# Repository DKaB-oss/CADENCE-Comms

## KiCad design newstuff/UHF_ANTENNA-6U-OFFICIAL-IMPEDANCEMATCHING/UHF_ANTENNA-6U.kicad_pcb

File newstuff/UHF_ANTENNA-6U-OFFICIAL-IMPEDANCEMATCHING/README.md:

CADENCE UHF/L1 BANDS ANTENNA BOARD

6-layer PCB designed for CADENCE's UHF canted turnstile antenna and GPS L1 patch antenna. The board contains the UHF phasing network, antenna impedance-matching circuitry, power circuitry, and a burn-wire deployment circuit.

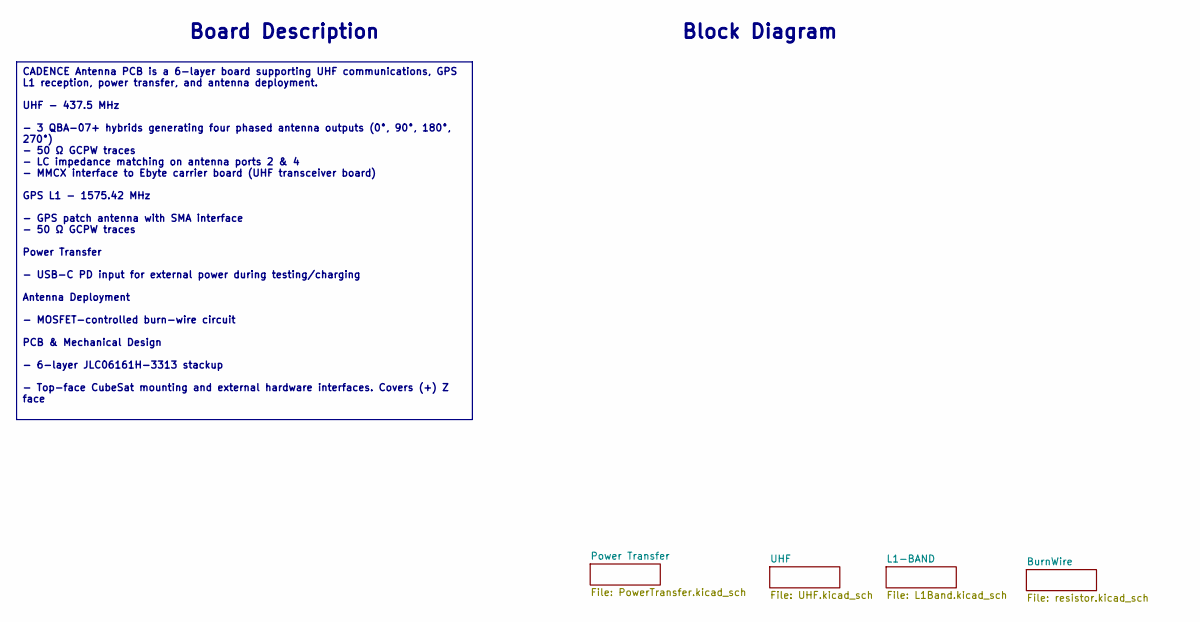
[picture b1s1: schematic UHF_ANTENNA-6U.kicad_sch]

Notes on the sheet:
Board Description
Block Diagram
CADENCE Antenna PCB is a 6-layer board supporting UHF communications, GPS L1 reception, power transfer, and antenna deployment. UHF - 437.5 MHz - 3 QBA-07+ hybrids generating four phased antenna outputs (0°, 90°, 180°, 270°) - 50 Ω GCPW traces - LC impedance matching on antenna ports 2 & 4 - MMCX i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

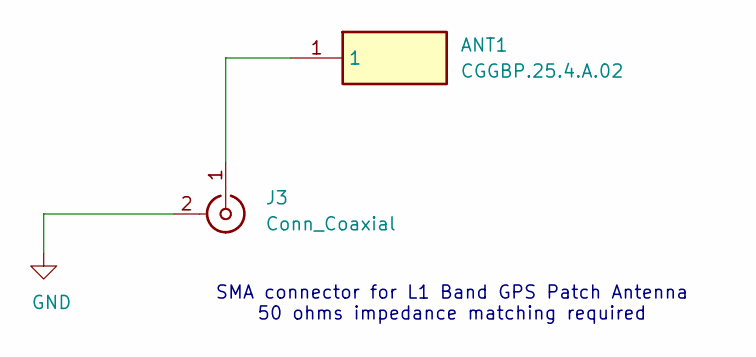
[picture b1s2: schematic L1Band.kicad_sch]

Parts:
ANT1: CGGBP.25.4.A.02; CGGBP254A02; Mouser Part Number 960-CGGBP.25.4.A.02
J3: Conn_Coaxial; SMA_Amphenol_132134-11_Vertical

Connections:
GND: J3.2 (Ext); also elsewhere on the board
unnamed: ANT1.1 (1_1), J3.1 (In)

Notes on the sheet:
SMA connector for L1 Band GPS Patch Antenna 50 ohms impedance matching required

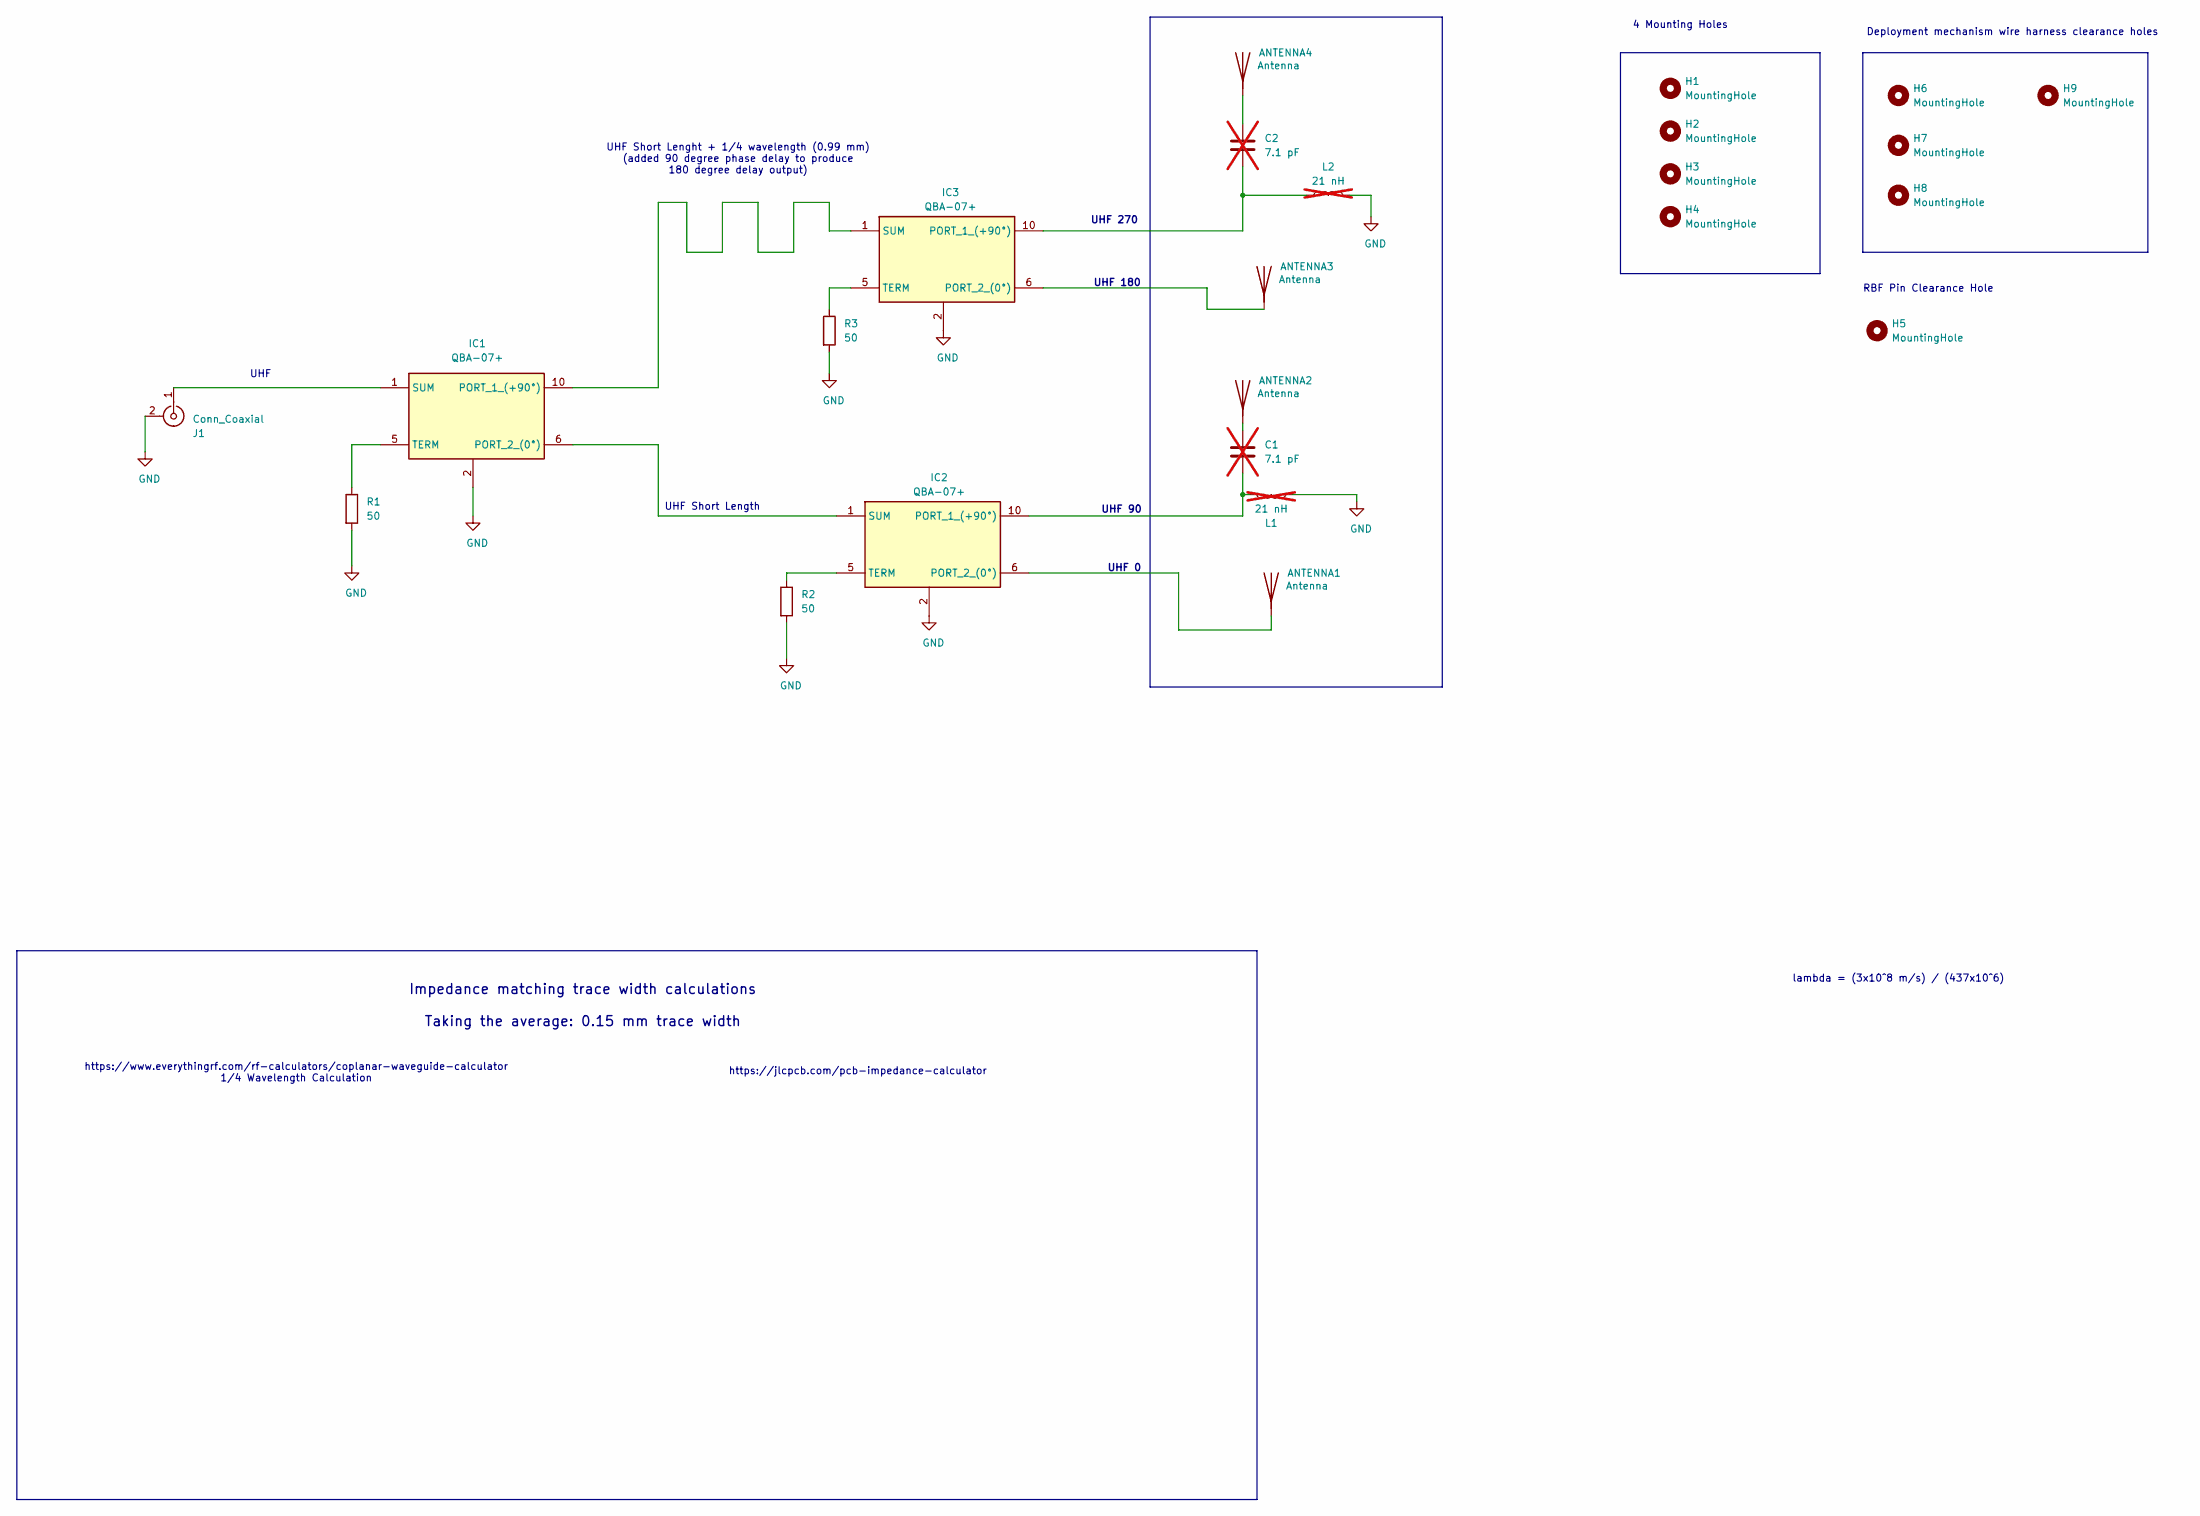
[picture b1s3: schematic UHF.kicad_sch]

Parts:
ANTENNA1, ANTENNA2, ANTENNA3, ANTENNA4: Antenna; SolderWirePad_1x01_SMD_5x10mm
C1, C2: 7.1 pF; C_0603_1608Metric; not fitted
H1, H2, H3, H4, H5: MountingHole; MountingHole_3.2mm_M3
H6, H7, H8, H9: MountingHole; MountingHole_2.7mm_M2.5_Pad
IC1, IC2, IC3: QBA-07+; QBA07; Manufacturer_Part_Number QBA-07+
J1: Conn_Coaxial; WR-MMCX_Wuerth_66012102111404_Vertical
L1, L2: 21 nH; L_0603_1608Metric; not fitted
R1, R2, R3: 50; R_0603_1608Metric

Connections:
GND: IC1.2, IC1.3 (GROUND_2), IC1.4 (GROUND_3), IC1.7 (GROUND_4), IC1.8 (GROUND_5), IC1.9 (GROUND_6), IC2.2, IC2.3 (GROUND_2), IC2.4 (GROUND_3), IC2.7 (GROUND_4), IC2.8 (GROUND_5), IC2.9 (GROUND_6), IC3.2, IC3.3 (GROUND_2), IC3.4 (GROUND_3), IC3.7 (GROUND_4), IC3.8 (GROUND_5), IC3.9 (GROUND_6), J1.2 (Ext), L1.1, L2.2, R1.2, R2.2, R3.2; also elsewhere on the board
unnamed: ANTENNA1.1 (A_1), IC2.6 (PORT_2_(0°))
unnamed: ANTENNA2.1 (A_1), C1.2
unnamed: ANTENNA3.1 (A_1), IC3.6 (PORT_2_(0°))
unnamed: ANTENNA4.1 (A_1), C2.1
unnamed: IC1.10 (PORT_1_(+90°)), IC3.1 (SUM)
unnamed: IC1.6 (PORT_2_(0°)), IC2.1 (SUM)
unnamed: IC1.1 (SUM), J1.1 (In)
unnamed: IC1.5 (TERM), R1.1
unnamed: C1.1, IC2.10 (PORT_1_(+90°)), L1.2
unnamed: IC2.5 (TERM), R2.1
unnamed: C2.2, IC3.10 (PORT_1_(+90°)), L2.1
unnamed: IC3.5 (TERM), R3.1

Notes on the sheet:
UHF
https://www.everythingrf.com/rf-calculators/coplanar-waveguide-calculator 1/4 Wavelength Calculation
UHF Short Length
UHF Short Lenght + 1/4 wavelength (0.99 mm) (added 90 degree phase delay to produce 180 degree delay output)
lambda = (3x10^8 m/s) / (437x10^6)
UHF 90
UHF 270
Impedance matching trace width calculations Taking the average: 0.15 mm trace width
RBF Pin Clearance Hole
UHF 0
UHF 180
https://jlcpcb.com/pcb-impedance-calculator
Deployment mechanism wire harness clearance holes
4 Mounting Holes

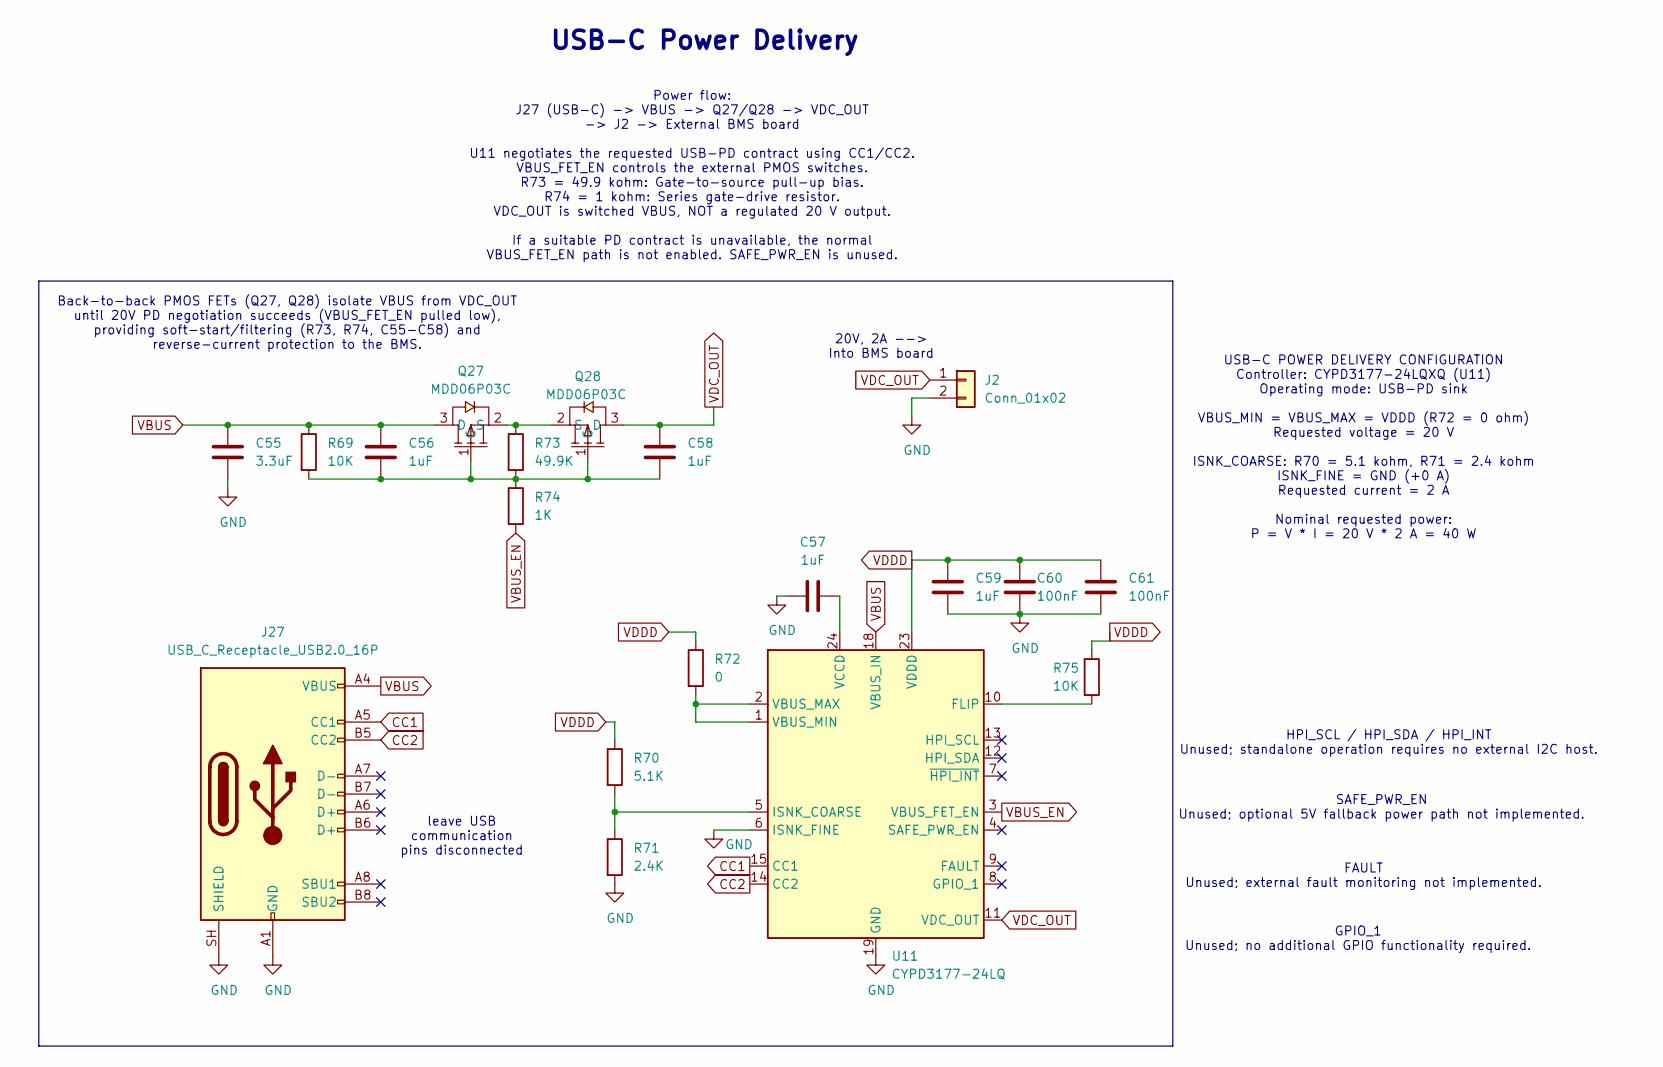
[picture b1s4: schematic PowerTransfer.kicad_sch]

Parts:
C55: 3.3uF; C_0805_2012Metric
C56, C57, C58, C59: 1uF; C_0805_2012Metric
C60, C61: 100nF; C_0603_1608Metric
J2: Conn_01x02; TerminalBlock_RND_205-00276_1x02_P5.00mm_Vertical
J27: USB_C_Receptacle_USB2.0_16P; USB_C_Receptacle_GCT_USB4110
Q27, Q28: MDD06P03C; SOT-23-3L_L2.9-W1.6-P1.90-LS2.8-BL; MPN MDD06P03C; LCSC Part C53069233
R69: 10K; R_0603_1608Metric_Pad0.98x0.95mm_HandSolder
R70: 5.1K; R_0603_1608Metric_Pad0.98x0.95mm_HandSolder
R71: 2.4K; R_0603_1608Metric
R72: 0; R_0603_1608Metric
R73: 49.9K; R_0603_1608Metric
R74: 1K; R_0603_1608Metric
R75: 10K; R_0603_1608Metric
U11: CYPD3177-24LQ; QFN-24-1EP_4x4mm_P0.5mm_EP2.75x2.75mm

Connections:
CC1: J27.A5 (CC1), U11.15 (CC1)
CC2: J27.B5 (CC2), U11.14 (CC2)
GND: C55.2, C57.2, C59.2, C60.2, C61.2, J2.2, J27.A1 (GND), J27.A12 (GND), J27.B1 (GND), J27.B12 (GND), J27.SH (SHIELD), R71.2, U11.6 (ISNK_FINE), U11.19 (GND), U11.22 (GND), U11.25 (GND); also elsewhere on the board
unnamed: C56.2, C58.2, Q27.1 (G), Q28.1 (G), R69.2, R73.2, R74.1
unnamed: Q27.2 (S), Q28.2 (S), R73.1
unnamed: R75.2, U11.10 (FLIP)
unnamed: R70.2, R71.1, U11.5 (ISNK_COARSE)
unnamed: R72.2, U11.1 (VBUS_MIN), U11.2 (VBUS_MAX)
unnamed: C57.1, U11.24 (VCCD)
VBUS: C55.1, C56.1, J27.A4 (VBUS), J27.A9 (VBUS), J27.B4 (VBUS), J27.B9 (VBUS), Q27.3 (D), R69.1, U11.18 (VBUS_IN)
VBUS_EN: R74.2, U11.3 (VBUS_FET_EN)
VDC_OUT: C58.1, J2.1, Q28.3 (D), U11.11 (VDC_OUT)
VDDD: C59.1, C60.1, C61.1, R70.1, R72.1, R75.1, U11.23 (VDDD)

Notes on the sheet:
SAFE_PWR_EN Unused; optional 5V fallback power path not implemented.
20V, 2A --> Into BMS board
USB-C Power Delivery
FAULT Unused; external fault monitoring not implemented.
HPI_SCL / HPI_SDA / HPI_INT Unused; standalone operation requires no external I2C host.
USB-C POWER DELIVERY CONFIGURATION Controller: CYPD3177-24LQXQ (U11) Operating mode: USB-PD sink VBUS_MIN = VBUS_MAX = VDDD (R72 = 0 ohm) Requested voltage = 20 V ISNK_COARSE: R70 = 5.1 kohm, R71 = 2.4 kohm ISNK_FINE = GND (+0 A) Requested current = 2 A Nominal requested power: P = V * I = 20 V * 2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
Back-to-back PMOS FETs (Q27, Q28) isolate VBUS from VDC_OUT until 20V PD negotiation succeeds (VBUS_FET_EN pulled low), providing soft-start/filtering (R73, R74, C55-C58) and reverse-current protection to the BMS.
leave USB communication pins disconnected
Power flow: J27 (USB-C) -> VBUS -> Q27/Q28 -> VDC_OUT -> J2 -> External BMS board U11 negotiates the requested USB-PD contract using CC1/CC2. VBUS_FET_EN controls the external PMOS switches. R73 = 49.9 kohm: Gate-to-source pull-up bias. R74 = 1 kohm: Series gate-drive resistor. VDC_OUT is switched 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
GPIO_1 Unused; no additional GPIO functionality required.

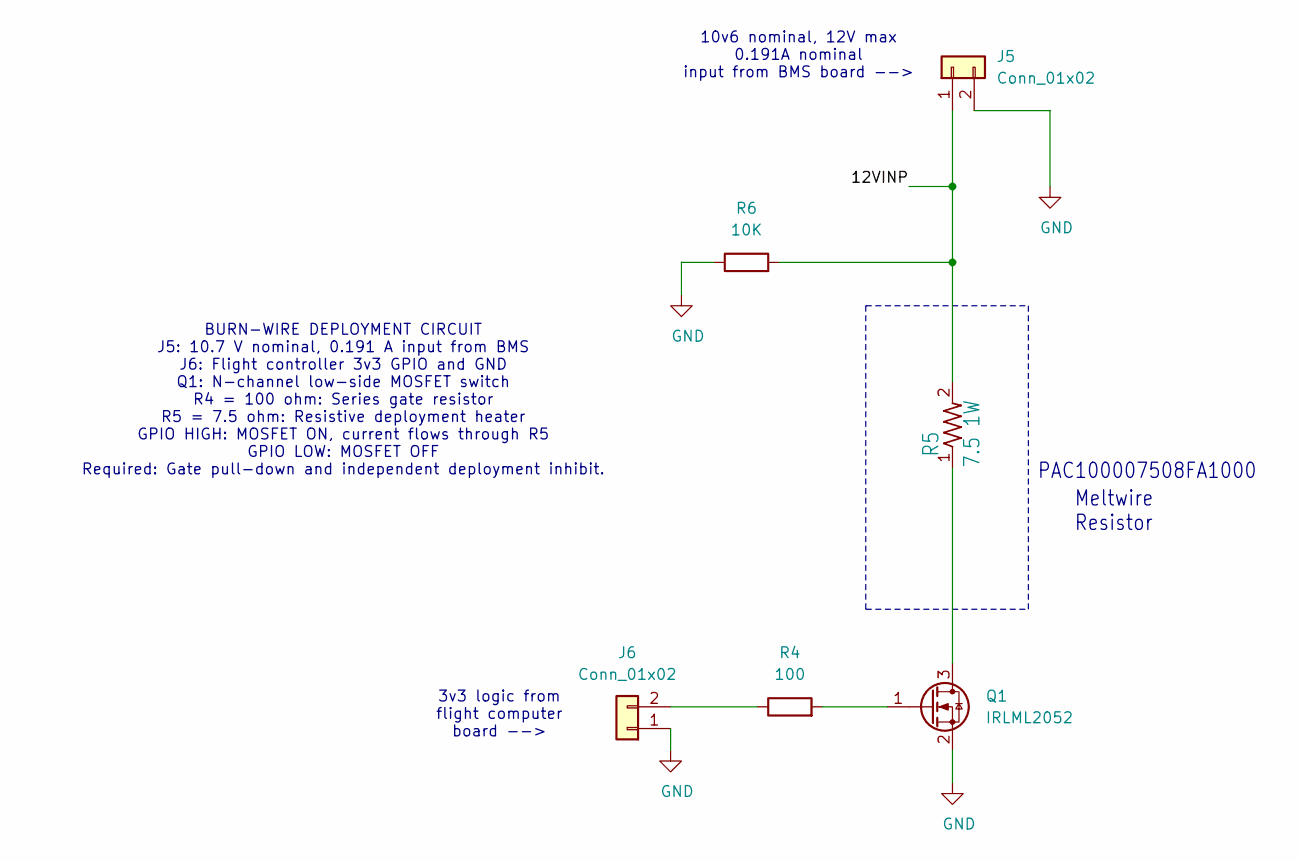
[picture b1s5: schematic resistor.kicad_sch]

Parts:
J5: Conn_01x02; JST_B2B-XH-A
J6: Conn_01x02; PinSocket_1x02_P2.54mm_Vertical_SMD_Pin1Left
Q1: IRLML2052; SOT-23
R4: 100; R_0603_1608Metric
R5: 7.5 1W; PAC01_VIS
R6: 10K; R_0603_1608Metric

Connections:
/BurnWire/12VINP: J5.1, R5.2, R6.2
GND: J5.2, J6.1, Q1.2 (S), R6.1; also elsewhere on the board
unnamed: J6.2, R4.1
unnamed: Q1.3 (D), R5.1
unnamed: Q1.1 (G), R4.2

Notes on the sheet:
10v6 nominal, 12V max 0.191A nominal input from BMS board -->
Meltwire Resistor
PAC100007508FA1000
3v3 logic from flight computer board -->
BURN-WIRE DEPLOYMENT CIRCUIT J5: 10.7 V nominal, 0.191 A input from BMS J6: Flight controller 3v3 GPIO and GND Q1: N-channel low-side MOSFET switch R4 = 100 ohm: Series gate resistor R5 = 7.5 ohm: Resistive deployment heater GPIO HIGH: MOSFET ON, current flows through R5 GPIO LOW: MOSFET OFF Requir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

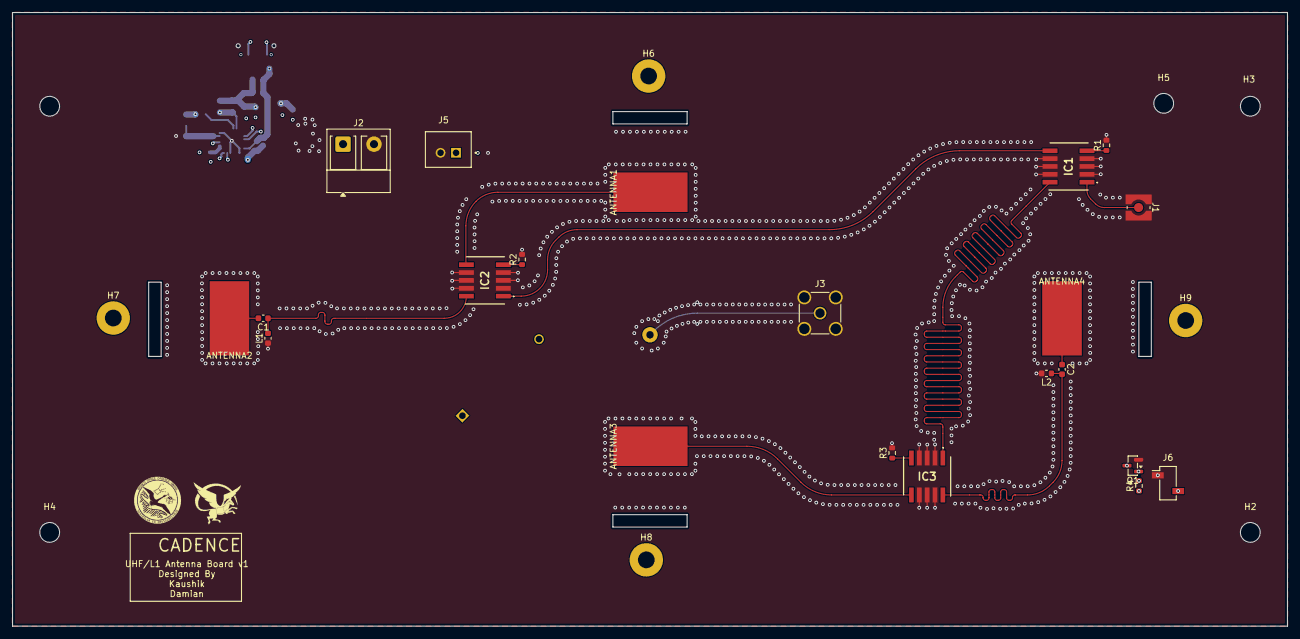
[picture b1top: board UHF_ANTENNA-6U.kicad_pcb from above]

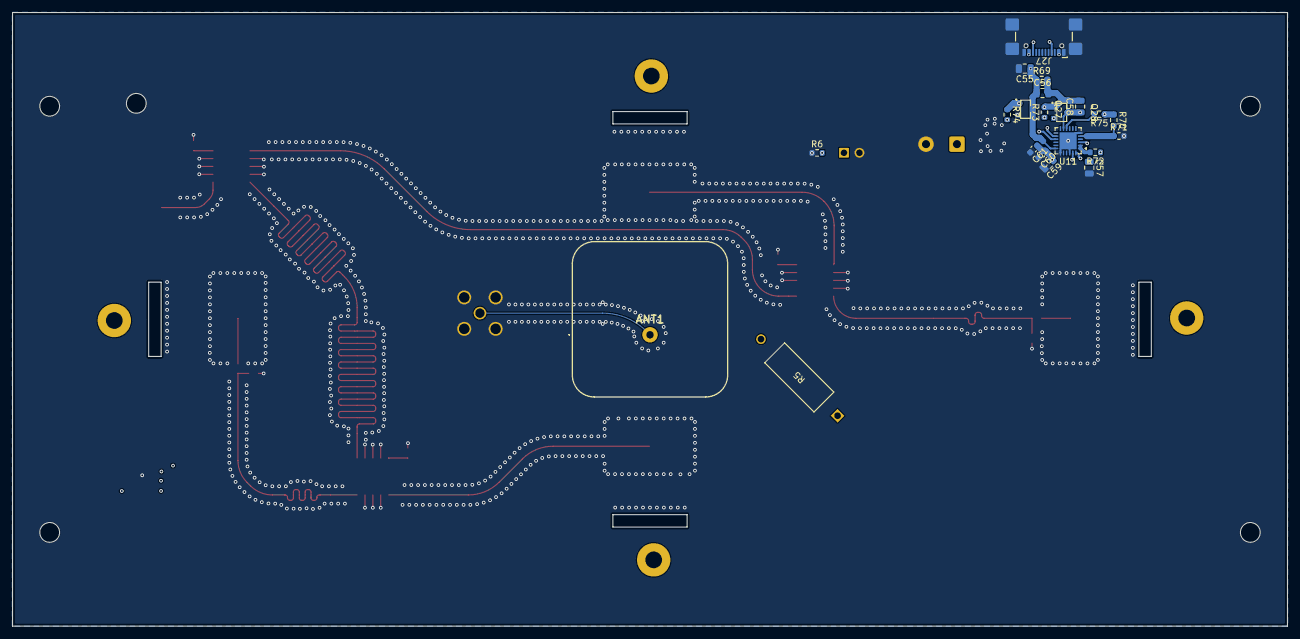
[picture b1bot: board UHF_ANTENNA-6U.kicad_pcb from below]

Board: 6 copper layers, 206.0 x 99.1 mm, 53 parts (21 on the bottom side), 30 nets.

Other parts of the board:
 : LOGO
 #2: LOGO
